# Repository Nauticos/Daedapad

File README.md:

# Daedapad

**Daedapad** is a macropad with 12 mechanical switches, 9 LEDs, a rotary encoder, and a 128x32 OLED display.

* Keyboard Maintainer: [Nathan LC](https://github.com/Nauticos)

**<ins>Features of Daedapad:</ins>**

* SEEED XIAO RP2040 (microcontroller)
* 12x MX-style switches arranged in a 3x4 pattern
* 9x SK6812MINI LEDs
* 1x EC11 rotary encoder
* 1x 128x32 OLED screen
* VIA compatability
* A custom sandwich mounting style case
* QMK Firmware

**<ins>BOM (Bill of Materials):</ins>**

* 1x SEEED XIAO RP2040 (microcontroller)
* 12x MX-style switches
* 12x Blank DSA keycaps
* 13x 1N4148 through-hole diodes
* 9x SK6812MINI LEDs
* 1x EC11 rotary encoder
* 1x 128x32 OLED screen
* 1x Custom sandwich mounting style case
* 1x Custom PCB
* 4x M3×16mm screws
* 4x M3×5×4mm heatset inserts

 This is a model of the casing I made in Autodesk Fusion, I have not got the hardware yet so I cannot upload a picture of that.

 Here is a screenshot of my schematic, I made it using KiCad.

Here is a screenshot of my PCB design, I made it using KiCad. You can access a demo of this at https://kicanvas.org/?repo=https%3A%2F%2Fgithub.com%2FNauticos%2FDaedapad%2Fblob%2Fmain%2FPCB%2Fhackpad.kicad_pcb.

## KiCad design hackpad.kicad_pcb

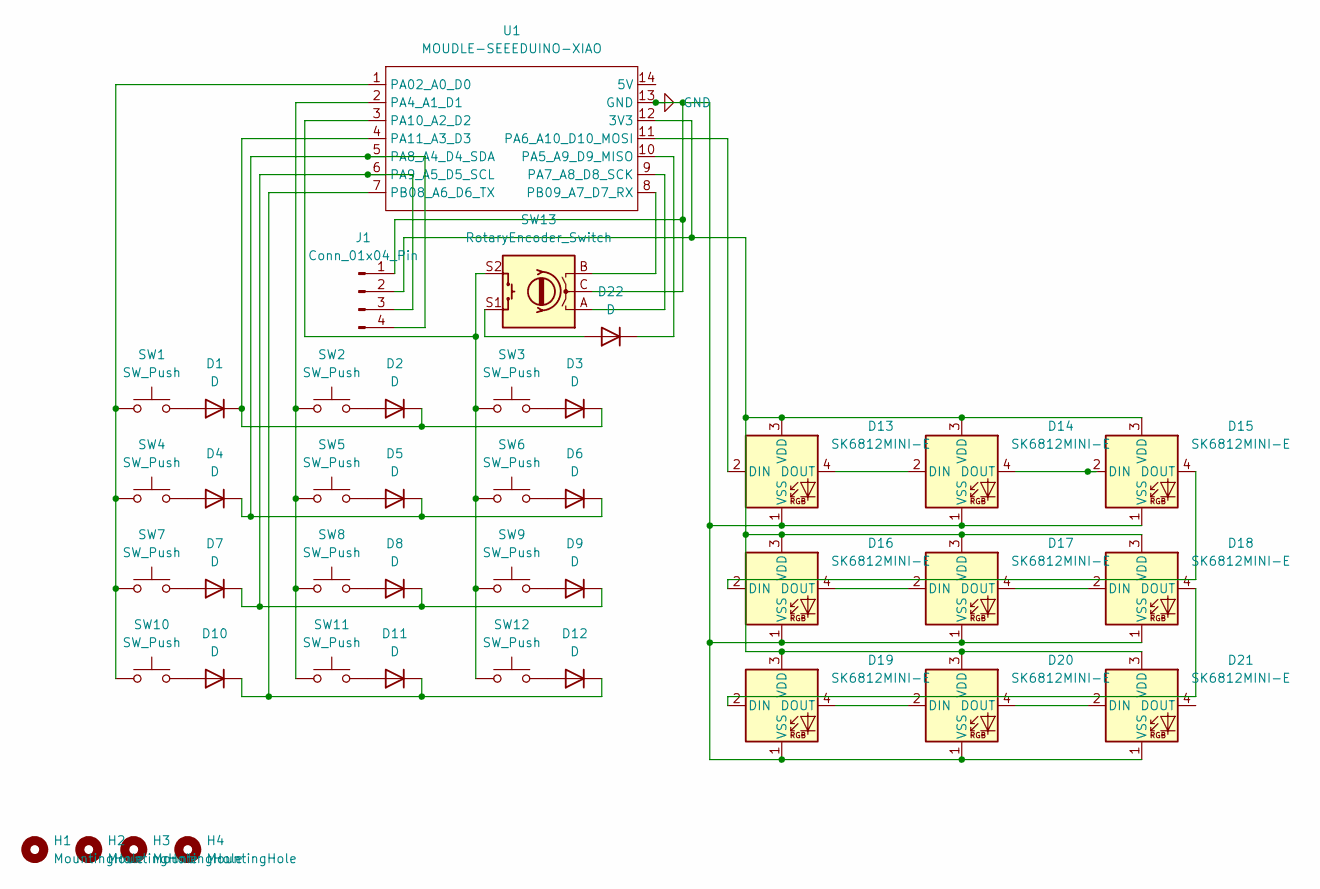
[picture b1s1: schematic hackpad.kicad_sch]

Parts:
D1, D2, D3, D4, D5, D6, D7, D8, D9, D10, D11, D12, D22: D; D_DO-35_SOD27_P7.62mm_Horizontal
D13, D14, D15, D16, D17, D18, D19, D20, D21: SK6812MINI-E; SK6812MINI-E_fixed
H1, H2, H3, H4: MountingHole; MountingHole_2.5mm
J1: Conn_01x04_Pin; ER_OLEDM0.91_1x-I2C
SW1, SW2, SW3, SW4, SW5, SW6, SW7, SW8, SW9, SW10, SW11, SW12: SW_Push; SW_Cherry_MX_1.00u_PCB
SW13: RotaryEncoder_Switch; RotaryEncoder_Alps_EC11E-Switch_Vertical_H20mm
U1: MOUDLE-SEEEDUINO-XIAO; XIAO-Generic-Hybrid-14P-2.54-21X17.8MM

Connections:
GND: D13.1 (VSS), D14.1 (VSS), D15.1 (VSS), D16.1 (VSS), D17.1 (VSS), D18.1 (VSS), D19.1 (VSS), D20.1 (VSS), D21.1 (VSS), J1.1, SW13.C, U1.13 (GND)
unnamed: D1.2 (A), SW1.2
unnamed: D1.1 (K), D2.1 (K), D3.1 (K), U1.4 (PA11_A3_D3)
unnamed: D2.2 (A), SW2.2
unnamed: D3.2 (A), SW3.2
unnamed: D4.2 (A), SW4.2
unnamed: D4.1 (K), D5.1 (K), D6.1 (K), J1.4, U1.5 (PA8_A4_D4_SDA)
unnamed: D5.2 (A), SW5.2
unnamed: D6.2 (A), SW6.2
unnamed: D7.2 (A), SW7.2
unnamed: D7.1 (K), D8.1 (K), D9.1 (K), J1.3, U1.6 (PA9_A5_D5_SCL)
unnamed: D8.2 (A), SW8.2
unnamed: D9.2 (A), SW9.2
unnamed: D10.2 (A), SW10.2
unnamed: D10.1 (K), D11.1 (K), D12.1 (K), U1.7 (PB08_A6_D6_TX)
unnamed: D11.2 (A), SW11.2
unnamed: D12.2 (A), SW12.2
unnamed: D13.2 (DIN), U1.11 (PA6_A10_D10_MOSI)
unnamed: D13.4 (DOUT), D14.2 (DIN)
unnamed: D13.3 (VDD), D14.3 (VDD), D15.3 (VDD), D16.3 (VDD), D17.3 (VDD), D18.3 (VDD), D19.3 (VDD), D20.3 (VDD), D21.3 (VDD), J1.2, U1.12 (3V3)
unnamed: D14.4 (DOUT), D15.2 (DIN)
unnamed: D15.4 (DOUT), D16.2 (DIN)
unnamed: D16.4 (DOUT), D17.2 (DIN)
unnamed: D17.4 (DOUT), D18.2 (DIN)
unnamed: D18.4 (DOUT), D19.2 (DIN)
unnamed: D19.4 (DOUT), D20.2 (DIN)
unnamed: D20.4 (DOUT), D21.2 (DIN)
unnamed: D22.2 (A), SW13.S1
unnamed: D22.1 (K), U1.10 (PA5_A9_D9_MISO)
unnamed: SW1.1, SW4.1, SW7.1, SW10.1, U1.1 (PA02_A0_D0)
unnamed: SW2.1, SW5.1, SW8.1, SW11.1, U1.2 (PA4_A1_D1)
unnamed: SW13.A, U1.9 (PA7_A8_D8_SCK)
unnamed: SW3.1, SW6.1, SW9.1, SW12.1, SW13.S2, U1.3 (PA10_A2_D2)
unnamed: SW13.B, U1.8 (PB09_A7_D7_RX)

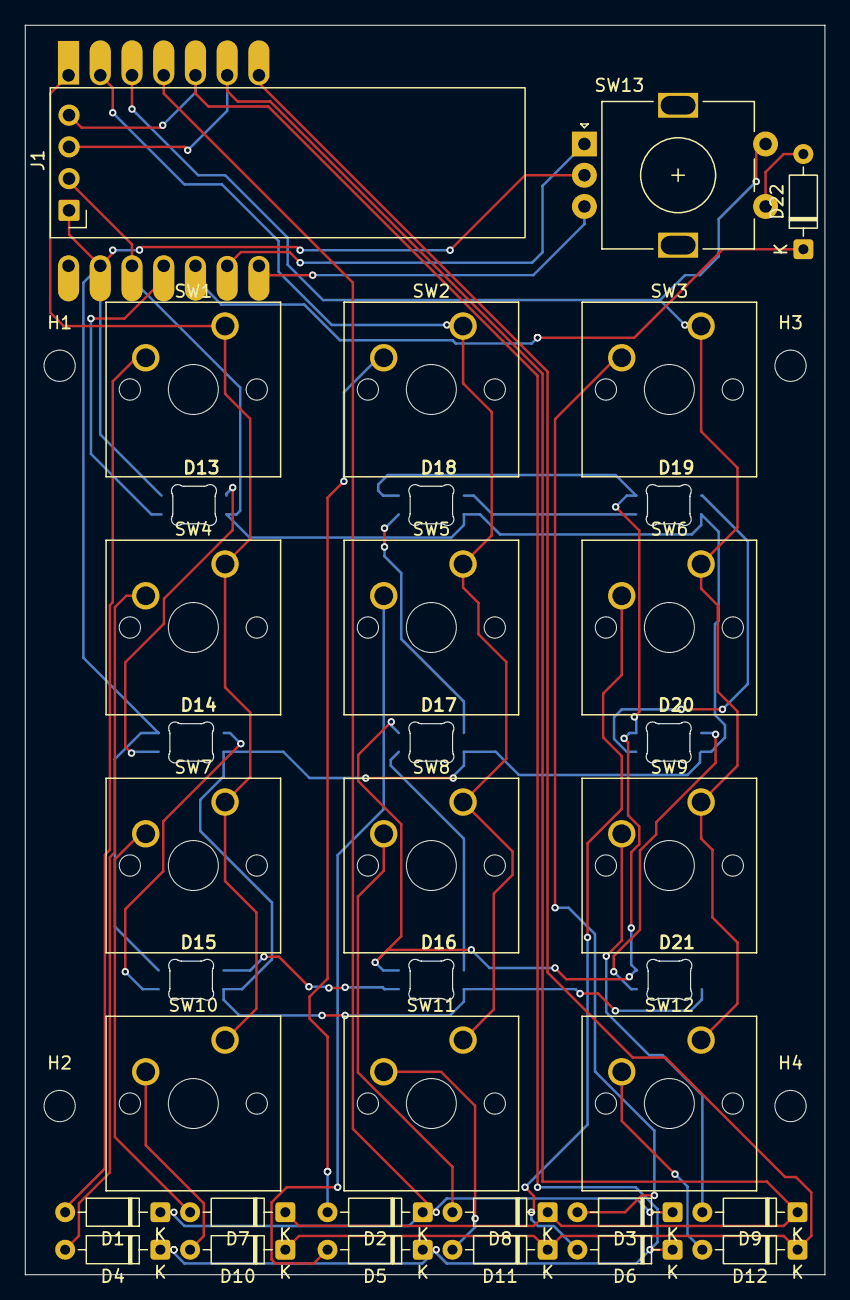
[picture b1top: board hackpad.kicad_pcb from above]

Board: 2 copper layers, 63.9 x 100.0 mm, 41 parts (1 on the bottom side), 34 nets.

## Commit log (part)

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2026-06-21 Added all my progress so far
    I am adding all of my progress so far
2026-06-21 Fix capitalization in project title
    Corrected the capitalization of 'Daedapad' in the README.
2026-06-21 Format features list in README.md as bullet points
2026-06-21 Added KiCad Stuff
    Added Schematic and PCB Design
2026-06-21 Updated README.md
    Updated README.md
2026-06-21 Updating README.md
    Added pictures of schematic and PCB and also a bit of text in the readme
2026-06-21 Sorted stuff into folders
    Made folders and put everything into the corresponding folder
2026-06-21 made rules.mk
    made rules.mk
2026-06-21 Added URL
2026-06-21 Added Assembled Product
2026-06-21 changed image name
2026-06-21 Fixed Images
2026-06-23 updated README.md final
2026-06-23 got rid of screws in README
2026-06-23 Updated Macropad Baseplate
2026-06-23 Updated README model picture
2026-06-23 Fixed pathways of images in README
2026-06-23 fixed bad grammar in README
2026-06-23 made format of the README consistent
2026-06-23 Added a full stop to the README
